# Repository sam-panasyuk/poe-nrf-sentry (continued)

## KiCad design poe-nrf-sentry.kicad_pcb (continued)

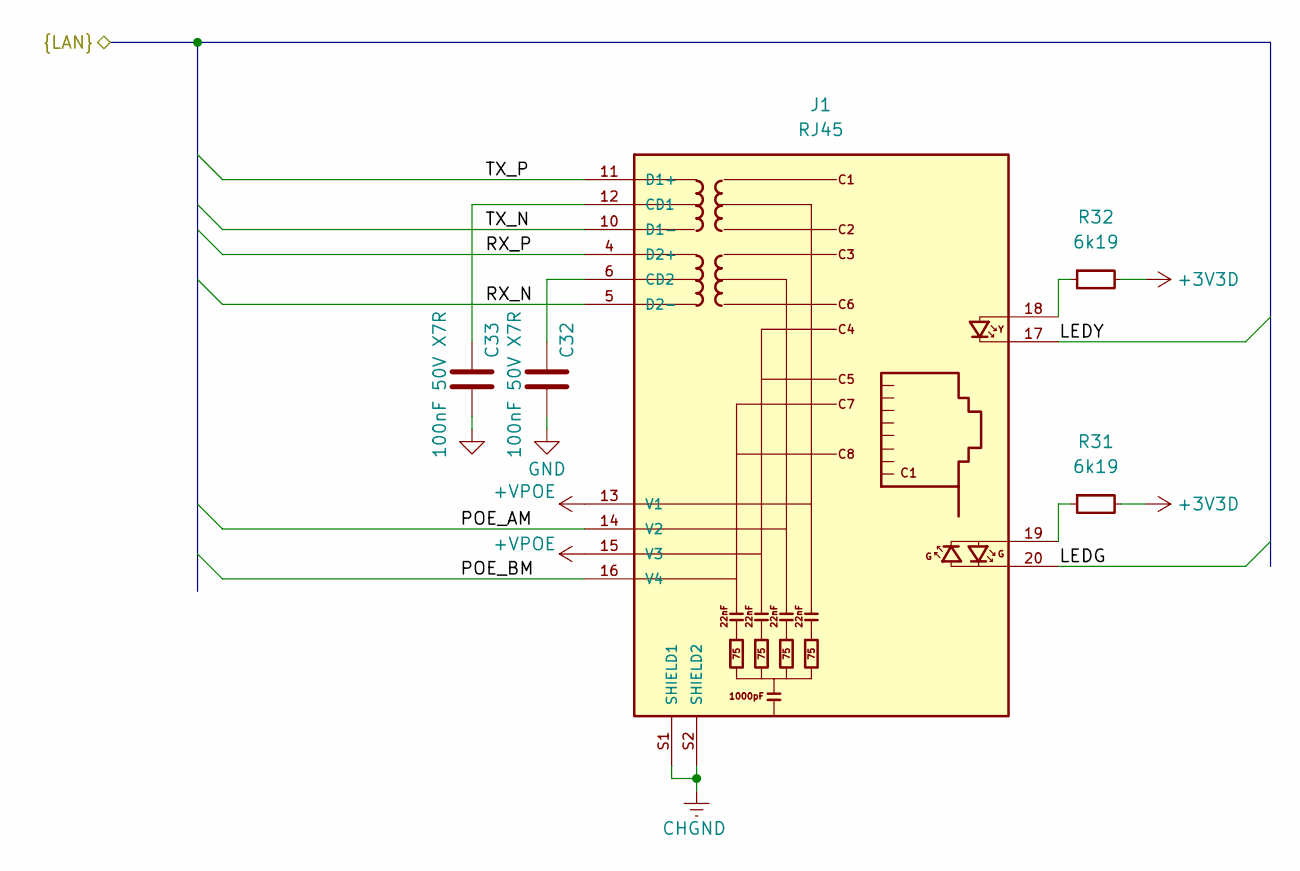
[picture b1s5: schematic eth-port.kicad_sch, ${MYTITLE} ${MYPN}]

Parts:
C32, C33: 100nF 50V X7R; C_0402_1005Metric; MPN CC0402KRX7R9BB104; JLCPN C131394
J1: RJ45; BEL_0826-1X1T-GH-F; MPN 0826-1X1T-GH-F
R31, R32: 6k19; R_0402_1005Metric; JLCPN C25914

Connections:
+3V3D: R31.2, R32.2; also elsewhere on the board
+VPOE: J1.13 (V1), J1.15 (V3); also elsewhere on the board
/eth-port1/LEDG: J1.20; also elsewhere on the board
/eth-port1/LEDY: J1.17; also elsewhere on the board
/eth-port1/POE_AM: J1.14 (V2); also elsewhere on the board
/eth-port1/POE_BM: J1.16 (V4); also elsewhere on the board
/eth-port1/RX_N: J1.5 (D2-); also elsewhere on the board
/eth-port1/RX_P: J1.4 (D2+); also elsewhere on the board
/eth-port1/TX_N: J1.10 (D1-); also elsewhere on the board
/eth-port1/TX_P: J1.11 (D1+); also elsewhere on the board
CHGND: J1.S1 (SHIELD1), J1.S2 (SHIELD2); also elsewhere on the board
GND: C32.1, C33.1; also elsewhere on the board
unnamed: C33.2, J1.12 (CD1)
unnamed: C32.2, J1.6 (CD2)
unnamed: J1.18, R32.1
unnamed: J1.19, R31.1

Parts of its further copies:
C34, C35: 100nF 50V X7R; C_0402_1005Metric; MPN CC0402KRX7R9BB104; JLCPN C131394
J2: RJ45; BEL_0826-1X1T-GH-F; MPN 0826-1X1T-GH-F
R33, R34: 6k19; R_0402_1005Metric; JLCPN C25914

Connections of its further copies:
+3V3D: R33.2, R34.2; also elsewhere on the board
+VPOE: J2.13 (V1), J2.15 (V3); also elsewhere on the board
/eth-port2/LEDG: J2.20; also elsewhere on the board
/eth-port2/LEDY: J2.17; also elsewhere on the board
/eth-port2/POE_AM: J2.14 (V2); also elsewhere on the board
/eth-port2/POE_BM: J2.16 (V4); also elsewhere on the board
/eth-port2/RX_N: J2.5 (D2-); also elsewhere on the board
/eth-port2/RX_P: J2.4 (D2+); also elsewhere on the board
/eth-port2/TX_N: J2.10 (D1-); also elsewhere on the board
/eth-port2/TX_P: J2.11 (D1+); also elsewhere on the board
CHGND: J2.S1 (SHIELD1), J2.S2 (SHIELD2); also elsewhere on the board
GND: C34.1, C35.1; also elsewhere on the board
unnamed: C34.2, J2.12 (CD1)
unnamed: C35.2, J2.6 (CD2)
unnamed: J2.18, R33.1
unnamed: J2.19, R34.1

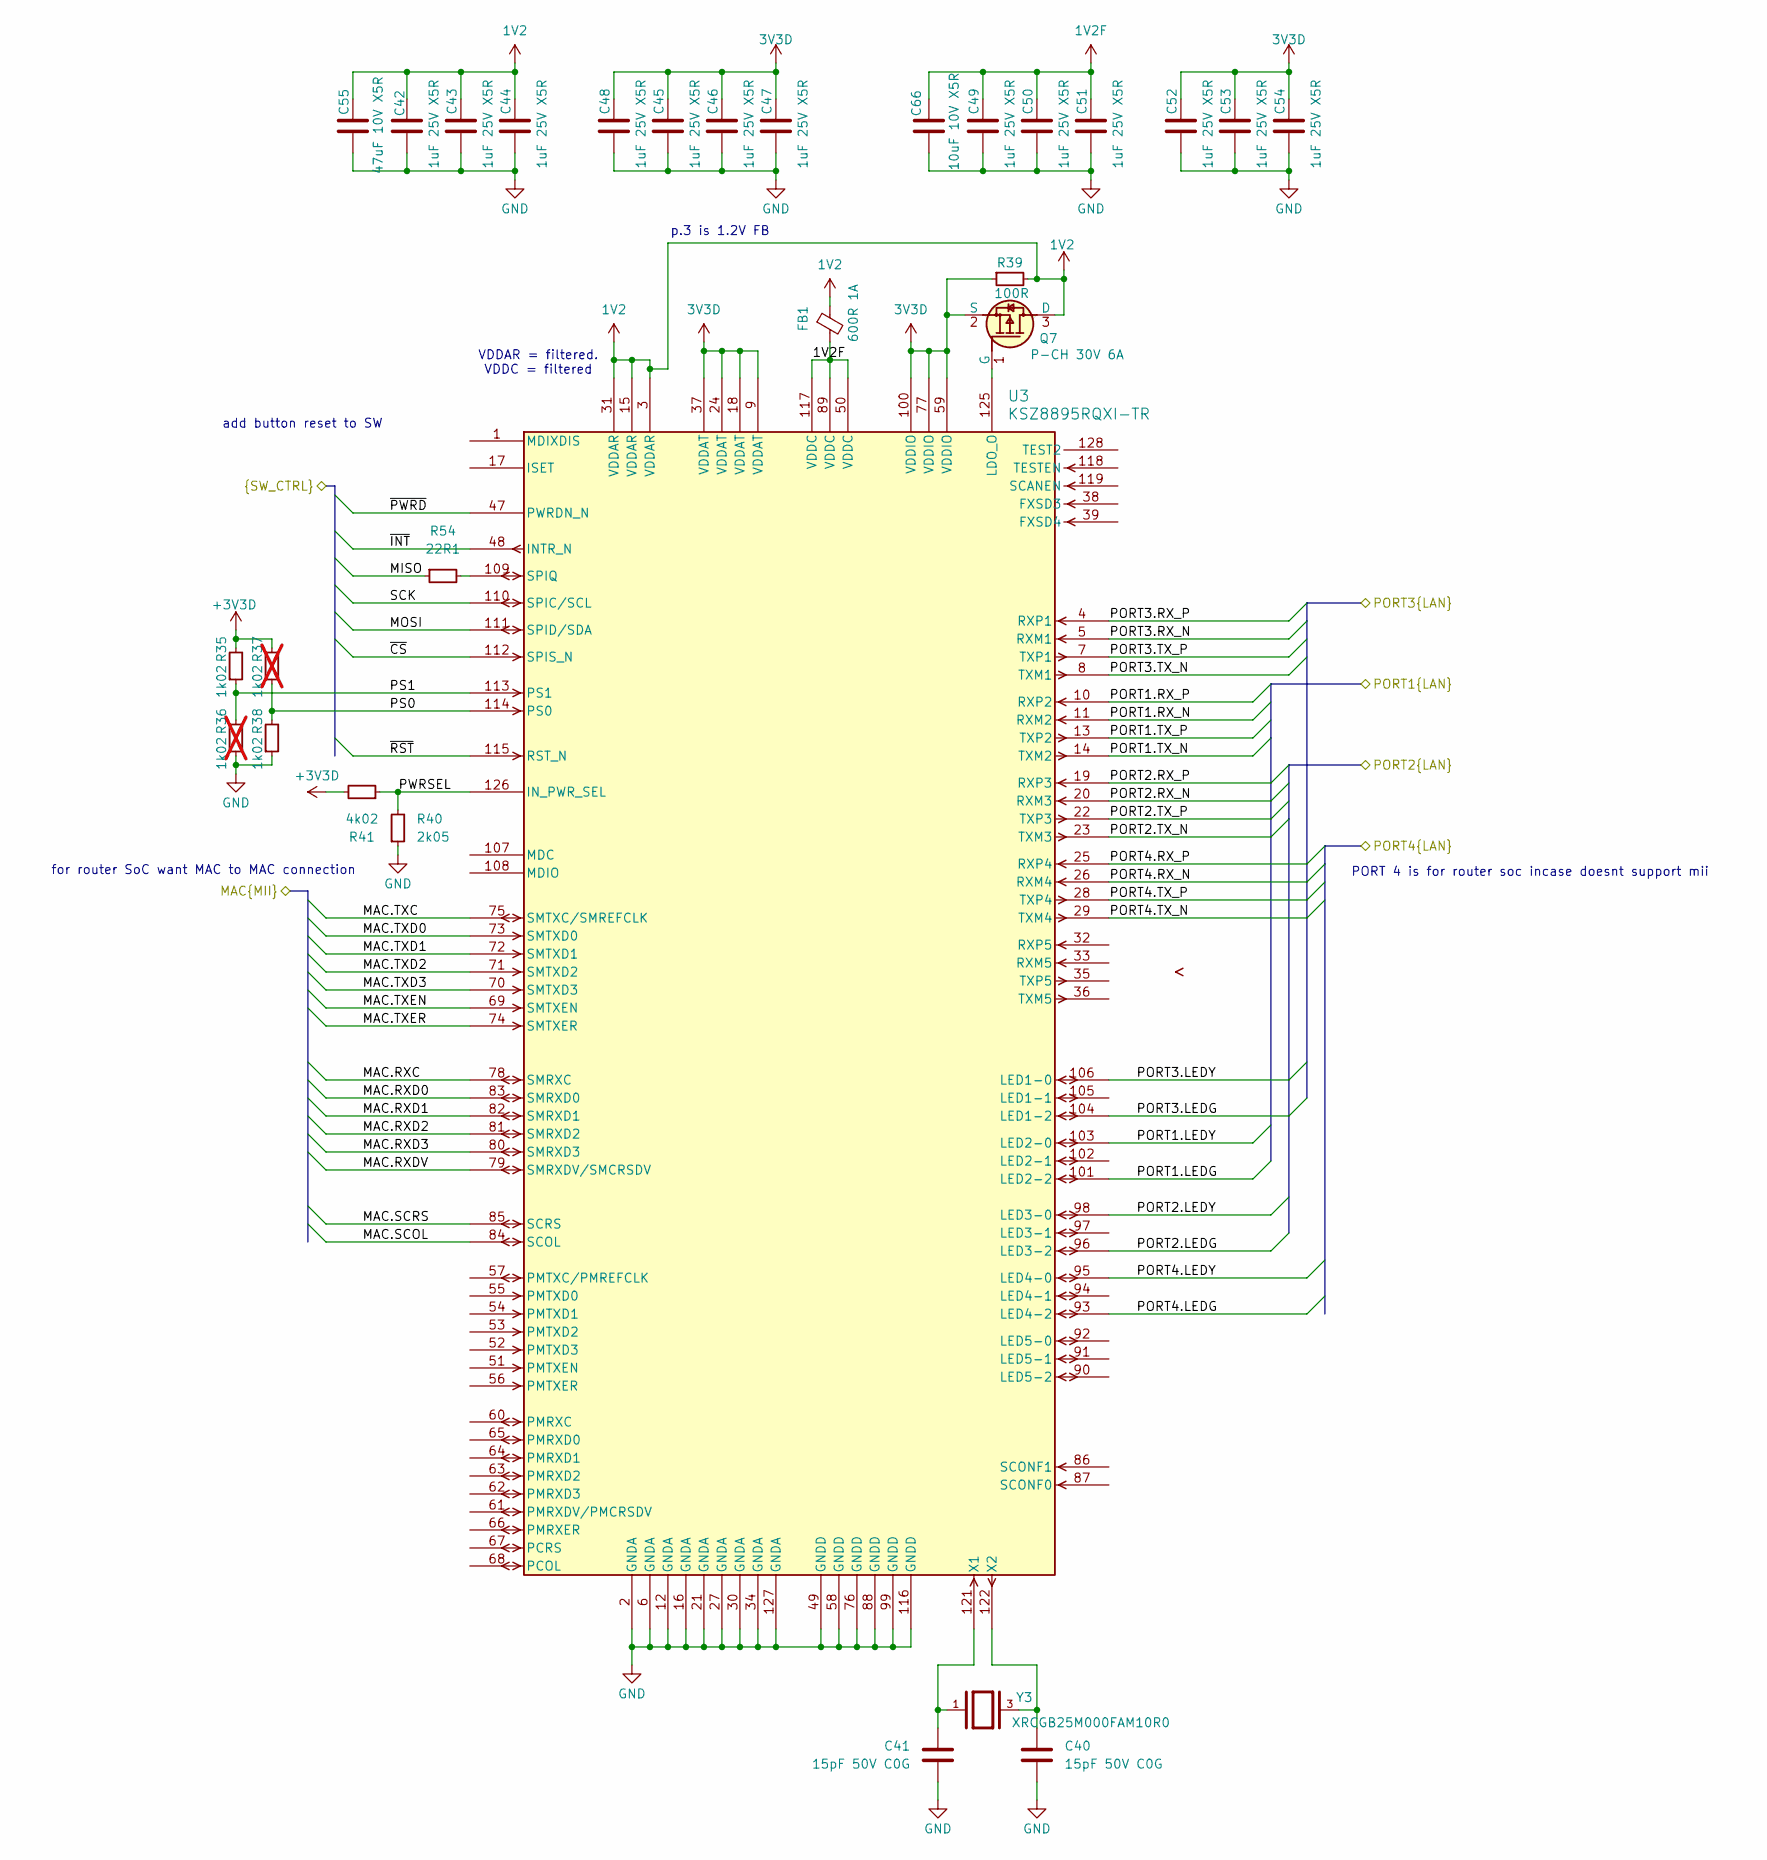
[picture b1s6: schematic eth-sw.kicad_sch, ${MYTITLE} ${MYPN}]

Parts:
C40, C41: 15pF 50V C0G; C_0402_1005Metric
C42, C43, C44, C45, C46, C47, C48, C49, C50, C51, C52, C53, C54: 1uF 25V X5R; C_0402_1005Metric; JLCPN C52923
C55: 47uF 10V X5R; C_0805_2012Metric; MPN C2012X5R1A476M125AC
C66: 10uF 10V X5R; C_0402_1005Metric
FB1: 600R 1A; FB_0603_1608Metric; MPN MPZ1608S601ATA00
Q7: P-CH 30V 6A; SOT-23-3; MPN SSM3J332R,LF
R35, R38: 1k02; R_0402_1005Metric; MPN RC0402FR-071K02L; JLCPN C163485
R36, R37: 1k02; R_0402_1005Metric; MPN RC0402FR-071K02L; JLCPN C163485; not fitted
R39: 100R; R_0402_1005Metric
R40: 2k05; R_0402_1005Metric; MPN AC0402FR-072K05L; JLCPN C100296
R41: 4k02; R_0402_1005Metric
R54: 22R1; R_0402_1005Metric; JLCPN C59651
U3: KSZ8895RQXI-TR; PQFP-128_MQL_MCH; MPN KSZ8895RQXI-TR
Y3: XRCGB25M000FAM10R0; MPN XRCGB25M000FAM10R0

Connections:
1V2: C42.1, C43.1, C44.1, C55.1, FB1.1, Q7.3 (D), R39.2, U3.3 (VDDAR), U3.15 (VDDAR), U3.31 (VDDAR)
1V2F: C49.1, C50.1, C51.1, C66.1, FB1.2, U3.50 (VDDC), U3.89 (VDDC), U3.117 (VDDC)
+3V3D: C45.1, C46.1, C47.1, C48.1, C52.1, C53.1, C54.1, Q7.2 (S), R35.2, R37.2, R39.1, R41.2, U3.9 (VDDAT), U3.18 (VDDAT), U3.24 (VDDAT), U3.37 (VDDAT), U3.59 (VDDIO), U3.77 (VDDIO), U3.100 (VDDIO); also elsewhere on the board
/eth-port1/LEDG: U3.101 (LED2-2); also elsewhere on the board
/eth-port1/LEDY: U3.103 (LED2-0); also elsewhere on the board
/eth-port1/RX_N: U3.11 (RXM2); also elsewhere on the board
/eth-port1/RX_P: U3.10 (RXP2); also elsewhere on the board
/eth-port1/TX_N: U3.14 (TXM2); also elsewhere on the board
/eth-port1/TX_P: U3.13 (TXP2); also elsewhere on the board
/eth-port2/LEDG: U3.96 (LED3-2); also elsewhere on the board
/eth-port2/LEDY: U3.98 (LED3-0); also elsewhere on the board
/eth-port2/RX_N: U3.20 (RXM3); also elsewhere on the board
/eth-port2/RX_P: U3.19 (RXP3); also elsewhere on the board
/eth-port2/TX_N: U3.23 (TXM3); also elsewhere on the board
/eth-port2/TX_P: U3.22 (TXP3); also elsewhere on the board
/eth-sw/MAC.RXC: U3.78 (SMRXC)
/eth-sw/MAC.RXD0: U3.83 (SMRXD0)
/eth-sw/MAC.RXD1: U3.82 (SMRXD1)
/eth-sw/MAC.RXD2: U3.81 (SMRXD2)
/eth-sw/MAC.RXD3: U3.80 (SMRXD3)
/eth-sw/MAC.RXDV: U3.79 (SMRXDV/SMCRSDV)
/eth-sw/MAC.SCOL: U3.84 (SCOL)
/eth-sw/MAC.SCRS: U3.85 (SCRS)
/eth-sw/MAC.TXC: U3.75 (SMTXC/SMREFCLK)
/eth-sw/MAC.TXD0: U3.73 (SMTXD0)
/eth-sw/MAC.TXD1: U3.72 (SMTXD1)
/eth-sw/MAC.TXD2: U3.71 (SMTXD2)
/eth-sw/MAC.TXD3: U3.70 (SMTXD3)
/eth-sw/MAC.TXEN: U3.69 (SMTXEN)
/eth-sw/MAC.TXER: U3.74 (SMTXER)
/eth-sw/MISO: R54.1; also elsewhere on the board
/eth-sw/MOSI: U3.111 (SPID/SDA); also elsewhere on the board
/eth-sw/PORT3.LEDG: U3.104 (LED1-2)
/eth-sw/PORT3.LEDY: U3.106 (LED1-0)
/eth-sw/PORT3.RX_N: U3.5 (RXM1); also elsewhere on the board
/eth-sw/PORT3.RX_P: U3.4 (RXP1); also elsewhere on the board
/eth-sw/PORT3.TX_N: U3.8 (TXM1); also elsewhere on the board
/eth-sw/PORT3.TX_P: U3.7 (TXP1); also elsewhere on the board
/eth-sw/PORT4.LEDG: U3.93 (LED4-2)
/eth-sw/PORT4.LEDY: U3.95 (LED4-0)
/eth-sw/PORT4.RX_N: U3.26 (RXM4)
/eth-sw/PORT4.RX_P: U3.25 (RXP4)
/eth-sw/PORT4.TX_N: U3.29 (TXM4)
/eth-sw/PORT4.TX_P: U3.28 (TXP4)
/eth-sw/PS0: R37.1, R38.2, U3.114 (PS0)
/eth-sw/PS1: R35.1, R36.2, U3.113 (PS1)
/eth-sw/PWRSEL: R40.2, R41.1, U3.126 (IN_PWR_SEL)
/eth-sw/~CS: U3.112 (SPIS_N); also elsewhere on the board
/eth-sw/~INT: U3.48 (INTR_N); also elsewhere on the board
/eth-sw/~PWRD: U3.47 (PWRDN_N); also elsewhere on the board
/eth-sw/~RST: U3.115 (RST_N); also elsewhere on the board
GND: C40.2, C41.2, C42.2, C43.2, C44.2, C45.2, C46.2, C47.2, C48.2, C49.2, C50.2, C51.2, C52.2, C53.2, C54.2, C55.2, C66.2, R36.1, R38.1, R40.1, U3.2 (GNDA), U3.6 (GNDA), U3.12 (GNDA), U3.16 (GNDA), U3.21 (GNDA), U3.27 (GNDA), U3.30 (GNDA), U3.34 (GNDA), U3.49 (GNDD), U3.58 (GNDD), U3.76 (GNDD), U3.88 (GNDD), U3.99 (GNDD), U3.116 (GNDD), U3.127 (GNDA); also elsewhere on the board
unnamed: Q7.1 (G), U3.125 (LDO_O)
unnamed: R54.2, U3.109 (SPIQ)
unnamed: C41.1, U3.121 (X1), Y3.1
unnamed: C40.1, U3.122 (X2), Y3.3

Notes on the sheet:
p.3 is 1.2V FB
add button reset to SW
PORT 4 is for router soc incase doesnt support mii
VDDAR = filtered. VDDC = filtered
for router SoC want MAC to MAC connection

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
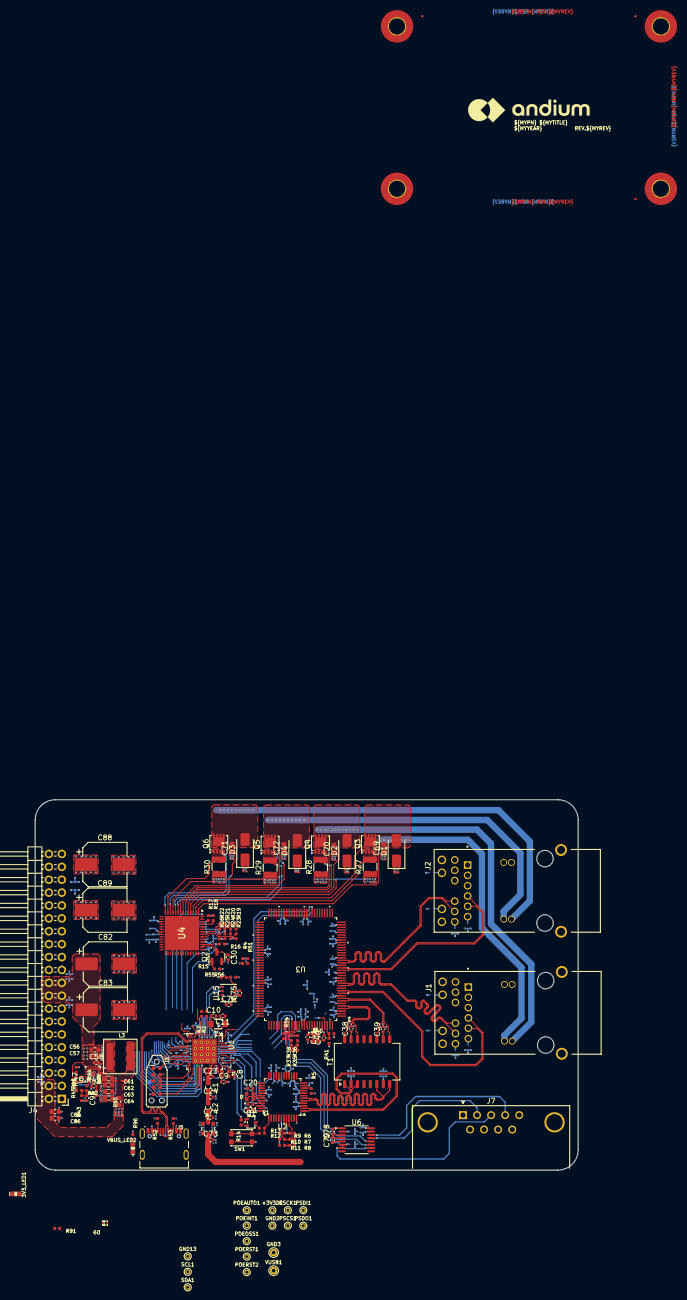
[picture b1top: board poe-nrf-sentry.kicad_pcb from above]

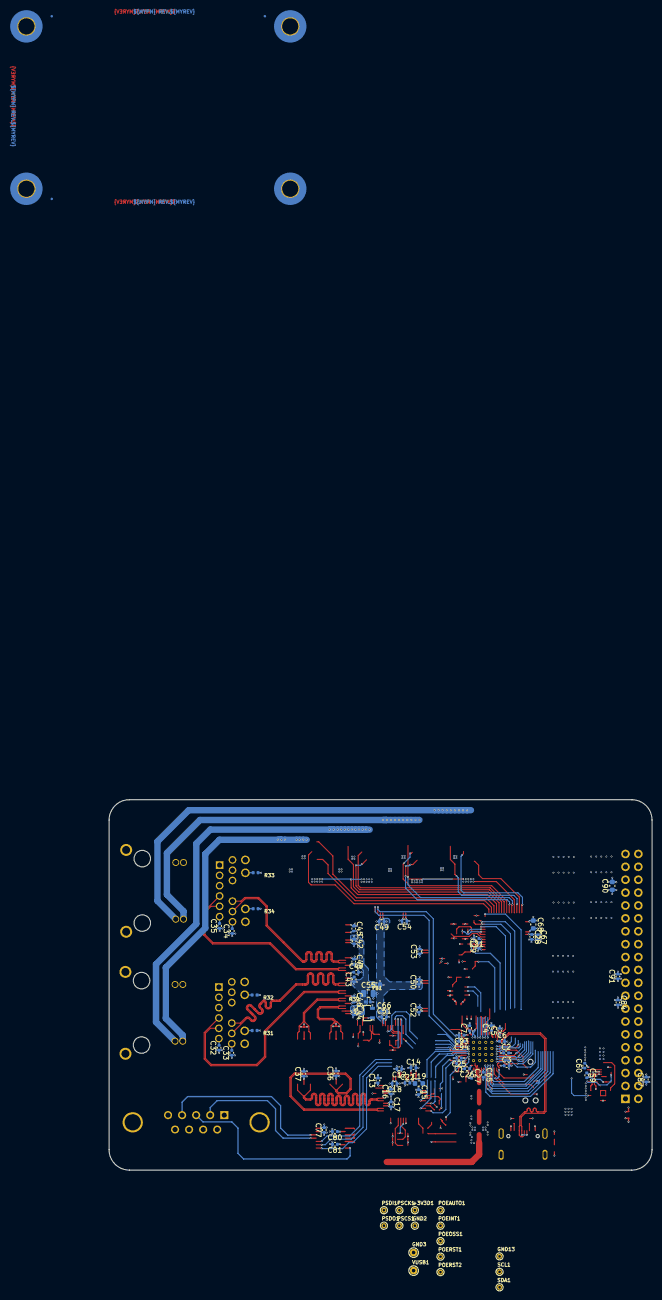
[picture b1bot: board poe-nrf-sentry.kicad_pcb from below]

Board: 4 copper layers, 107.0 x 73.0 mm, 216 parts (67 on the bottom side), 138 nets.

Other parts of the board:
C91: 100nF 50V X7R; C_0402_1005Metric

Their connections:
+12VD: C91.1; also elsewhere on the board
GND: C91.2; also elsewhere on the board
